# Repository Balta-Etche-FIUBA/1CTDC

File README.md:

"# 1CTDC" 
Esto es algo que sumo Git ni idea

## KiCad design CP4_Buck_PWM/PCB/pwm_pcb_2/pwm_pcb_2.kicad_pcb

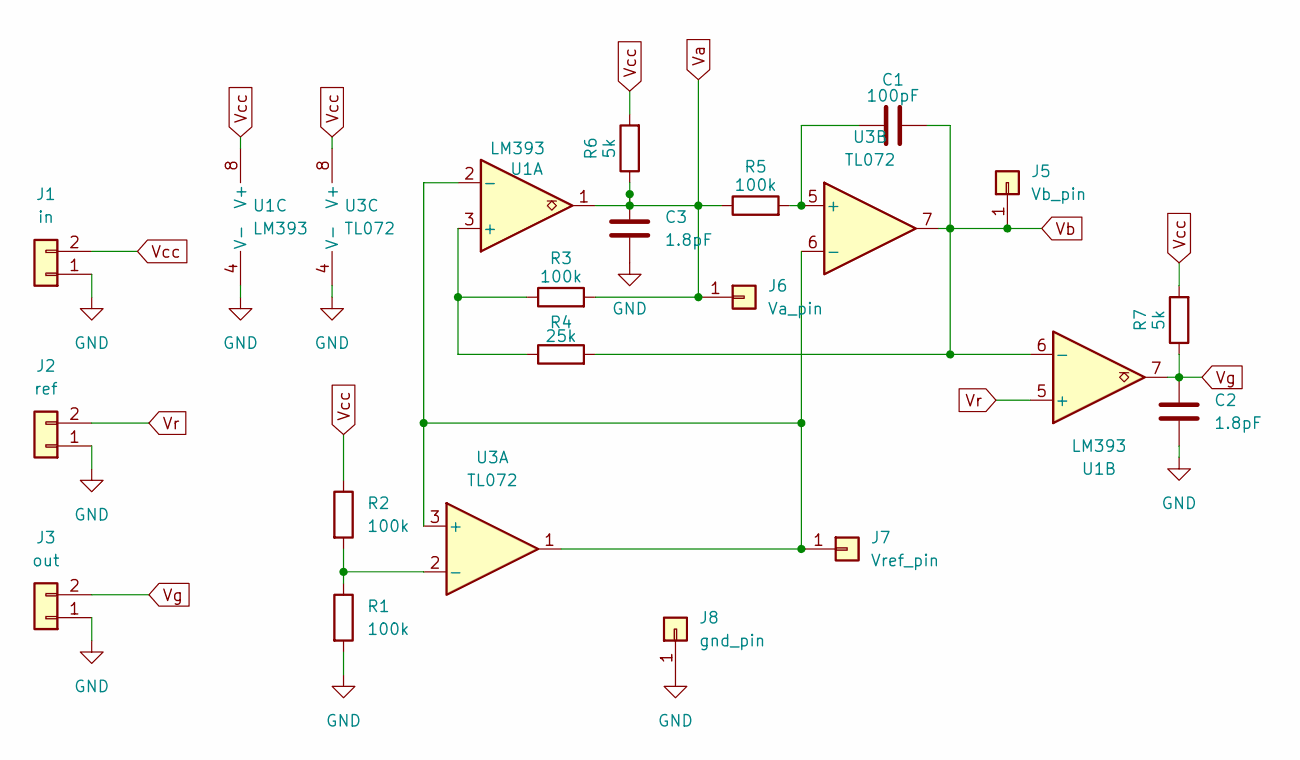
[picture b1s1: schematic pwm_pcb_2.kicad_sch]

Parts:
C1: 100pF; C_Disc_D4.3mm_W1.9mm_P5.00mm
C2, C3: 1.8pF; C_Disc_D4.3mm_W1.9mm_P5.00mm
J1: in; TerminalBlock_Phoenix_MKDS-1,5-2-5.08_1x02_P5.08mm_Horizont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
J2: ref; TerminalBlock_Phoenix_MKDS-1,5-2-5.08_1x02_P5.08mm_Horizont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
J3: out; TerminalBlock_Phoenix_MKDS-1,5-2-5.08_1x02_P5.08mm_Horizont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
J5: Vb_pin; PinHeader_1x01_P2.54mm_Vertical
J6: Va_pin; PinHeader_1x01_P2.54mm_Vertical
J7: Vref_pin; PinHeader_1x01_P2.54mm_Vertical
J8: gnd_pin; PinHeader_1x01_P2.54mm_Vertical
R1, R2, R3: 100k; R_Axial_DIN0204_L3.6mm_D1.6mm_P7.62mm_Horizontal
R4: 25k; R_Axial_DIN0204_L3.6mm_D1.6mm_P7.62mm_Horizontal
R5: 100k; Potentiometer_Bourns_3296W_Vertical
R6, R7: 5k; R_Axial_DIN0204_L3.6mm_D1.6mm_P7.62mm_Horizontal
U1: LM393; DIP-8_W7.62mm
U3: TL072; DIP-8_W7.62mm

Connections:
GND: C2.2, C3.2, J1.1, J2.1, J3.1, J8.1, R1.2, U1.4 (V-), U3.4 (V-)
unnamed: J7.1, U1.2 (-), U3.1, U3.3 (+), U3.6 (-)
unnamed: R3.1, R4.1, U1.3 (+)
unnamed: R1.1, R2.2, U3.2 (-)
unnamed: C1.1, R5.2, U3.5 (+)
Va: C3.1, J6.1, R3.2, R5.1, R6.1, U1.1
Vb: C1.2, J5.1, R4.2, U1.6 (-), U3.7
Vcc: J1.2, R2.1, R6.2, R7.2, U1.8 (V+), U3.8 (V+)
Vg: C2.1, J3.2, R7.1, U1.7
Vr: J2.2, U1.5 (+)

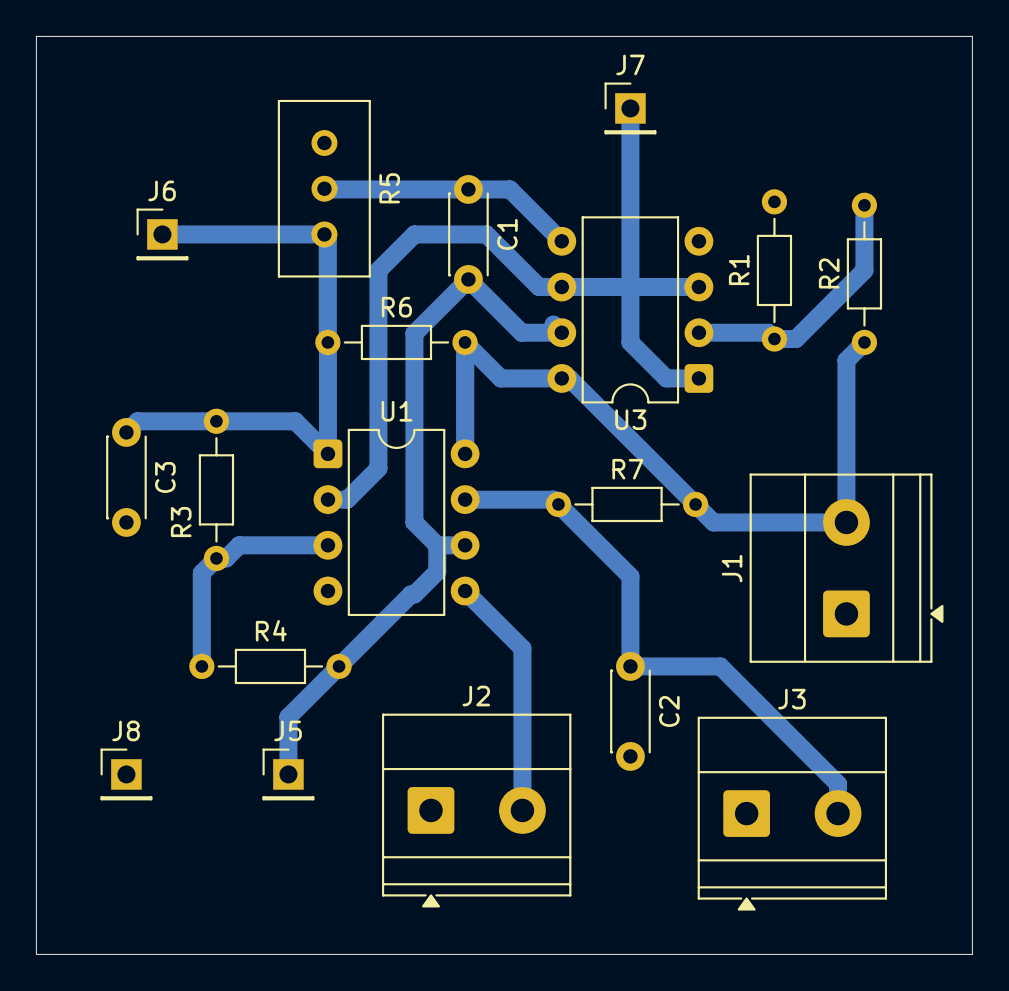
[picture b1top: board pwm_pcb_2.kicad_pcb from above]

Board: 2 copper layers, 52.0 x 51.0 mm, 19 parts (0 on the bottom side), 10 nets.

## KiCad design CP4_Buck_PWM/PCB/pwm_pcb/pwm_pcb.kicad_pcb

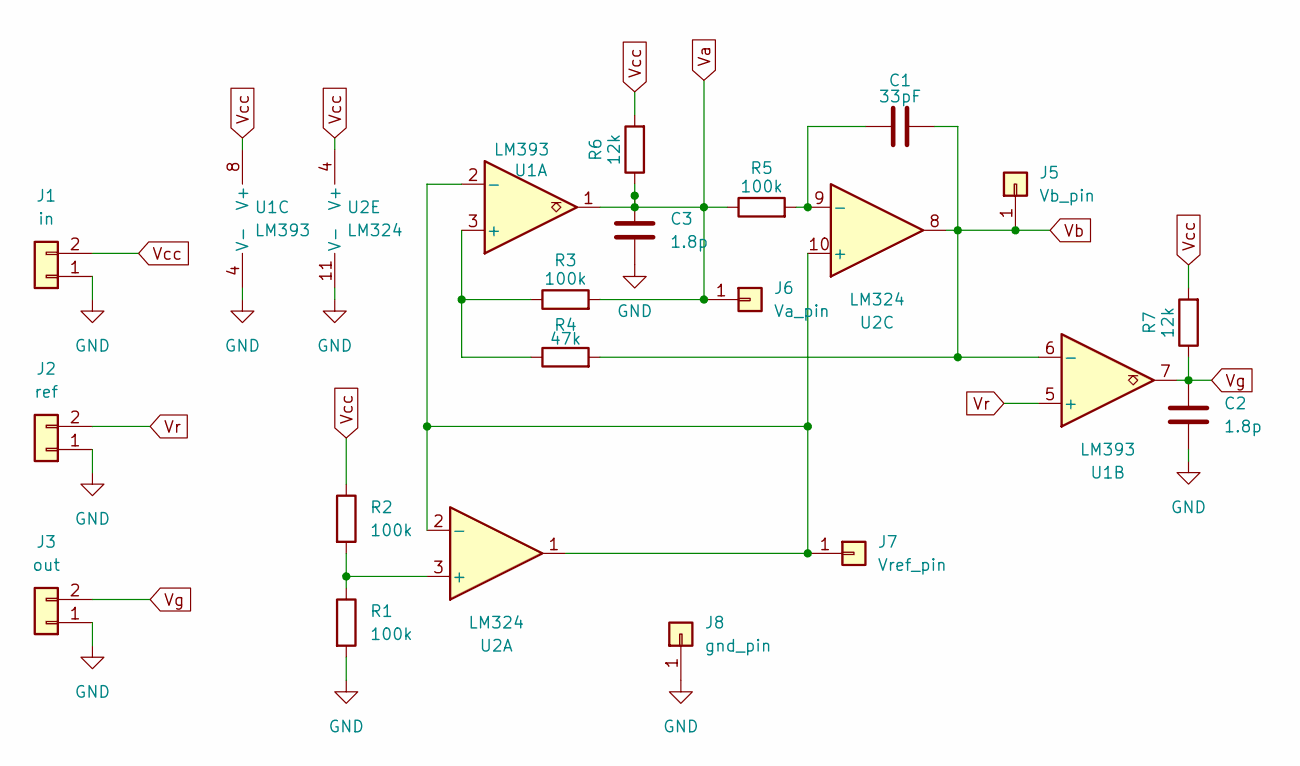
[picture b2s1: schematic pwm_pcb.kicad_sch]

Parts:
C1: 33pF; C_Disc_D3.0mm_W1.6mm_P2.50mm
C2, C3: 1.8p; C_Disc_D3.0mm_W1.6mm_P2.50mm
J1: in; TerminalBlock_Phoenix_MKDS-1,5-2-5.08_1x02_P5.08mm_Horizont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
J2: ref; TerminalBlock_Phoenix_MKDS-1,5-2-5.08_1x02_P5.08mm_Horizont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
J3: out; TerminalBlock_Phoenix_MKDS-1,5-2-5.08_1x02_P5.08mm_Horizont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
J5: Vb_pin; PinHeader_1x01_P2.54mm_Vertical
J6: Va_pin; PinHeader_1x01_P2.54mm_Vertical
J7: Vref_pin; PinHeader_1x01_P2.54mm_Vertical
J8: gnd_pin; PinHeader_1x01_P2.54mm_Vertical
R1, R2, R3: 100k; R_Axial_DIN0204_L3.6mm_D1.6mm_P5.08mm_Horizontal
R4: 47k; R_Axial_DIN0204_L3.6mm_D1.6mm_P5.08mm_Horizontal
R5: 100k; Potentiometer_Bourns_3296W_Vertical
R6, R7: 12k; R_Axial_DIN0204_L3.6mm_D1.6mm_P5.08mm_Horizontal
U1: LM393; DIP-8_W7.62mm
U2: LM324; DIP-14_W7.62mm

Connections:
GND: C2.2, C3.2, J1.1, J2.1, J3.1, J8.1, R1.2, U1.4 (V-), U2.11 (V-)
unnamed: J7.1, U1.2 (-), U2.1, U2.2 (-), U2.10 (+)
unnamed: R3.1, R4.1, U1.3 (+)
unnamed: R1.1, R2.2, U2.3 (+)
unnamed: C1.1, R5.2, U2.9 (-)
Va: C3.1, J6.1, R3.2, R5.1, R6.1, U1.1
Vb: C1.2, J5.1, R4.2, U1.6 (-), U2.8
Vcc: J1.2, R2.1, R6.2, R7.2, U1.8 (V+), U2.4 (V+)
Vg: C2.1, J3.2, R7.1, U1.7
Vr: J2.2, U1.5 (+)

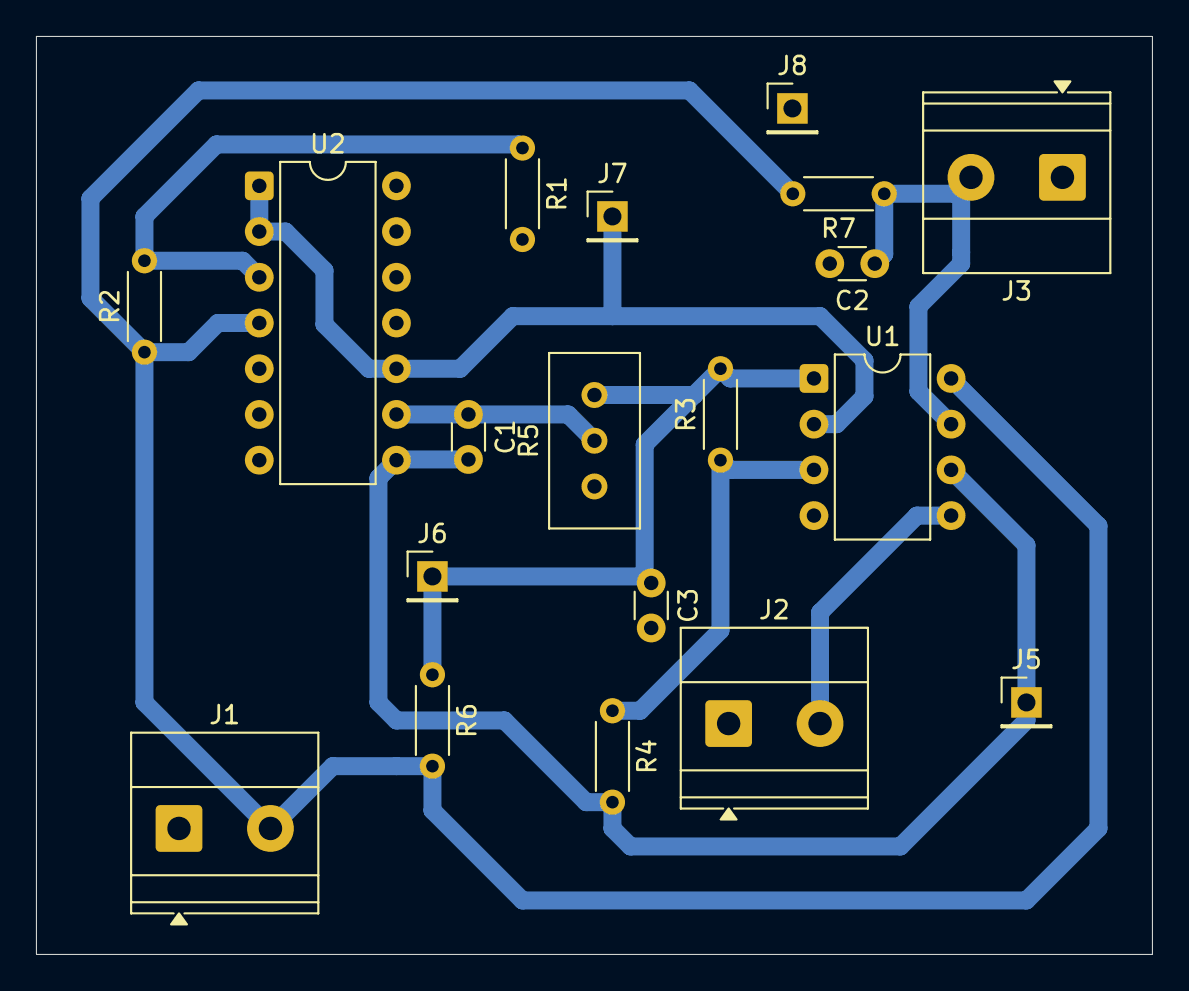
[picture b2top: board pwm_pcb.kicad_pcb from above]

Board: 2 copper layers, 62.0 x 51.0 mm, 19 parts (0 on the bottom side), 10 nets.

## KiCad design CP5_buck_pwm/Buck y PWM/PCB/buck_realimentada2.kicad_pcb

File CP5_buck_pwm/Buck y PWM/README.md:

Solo porque sino no me dejaba crear la carpeta

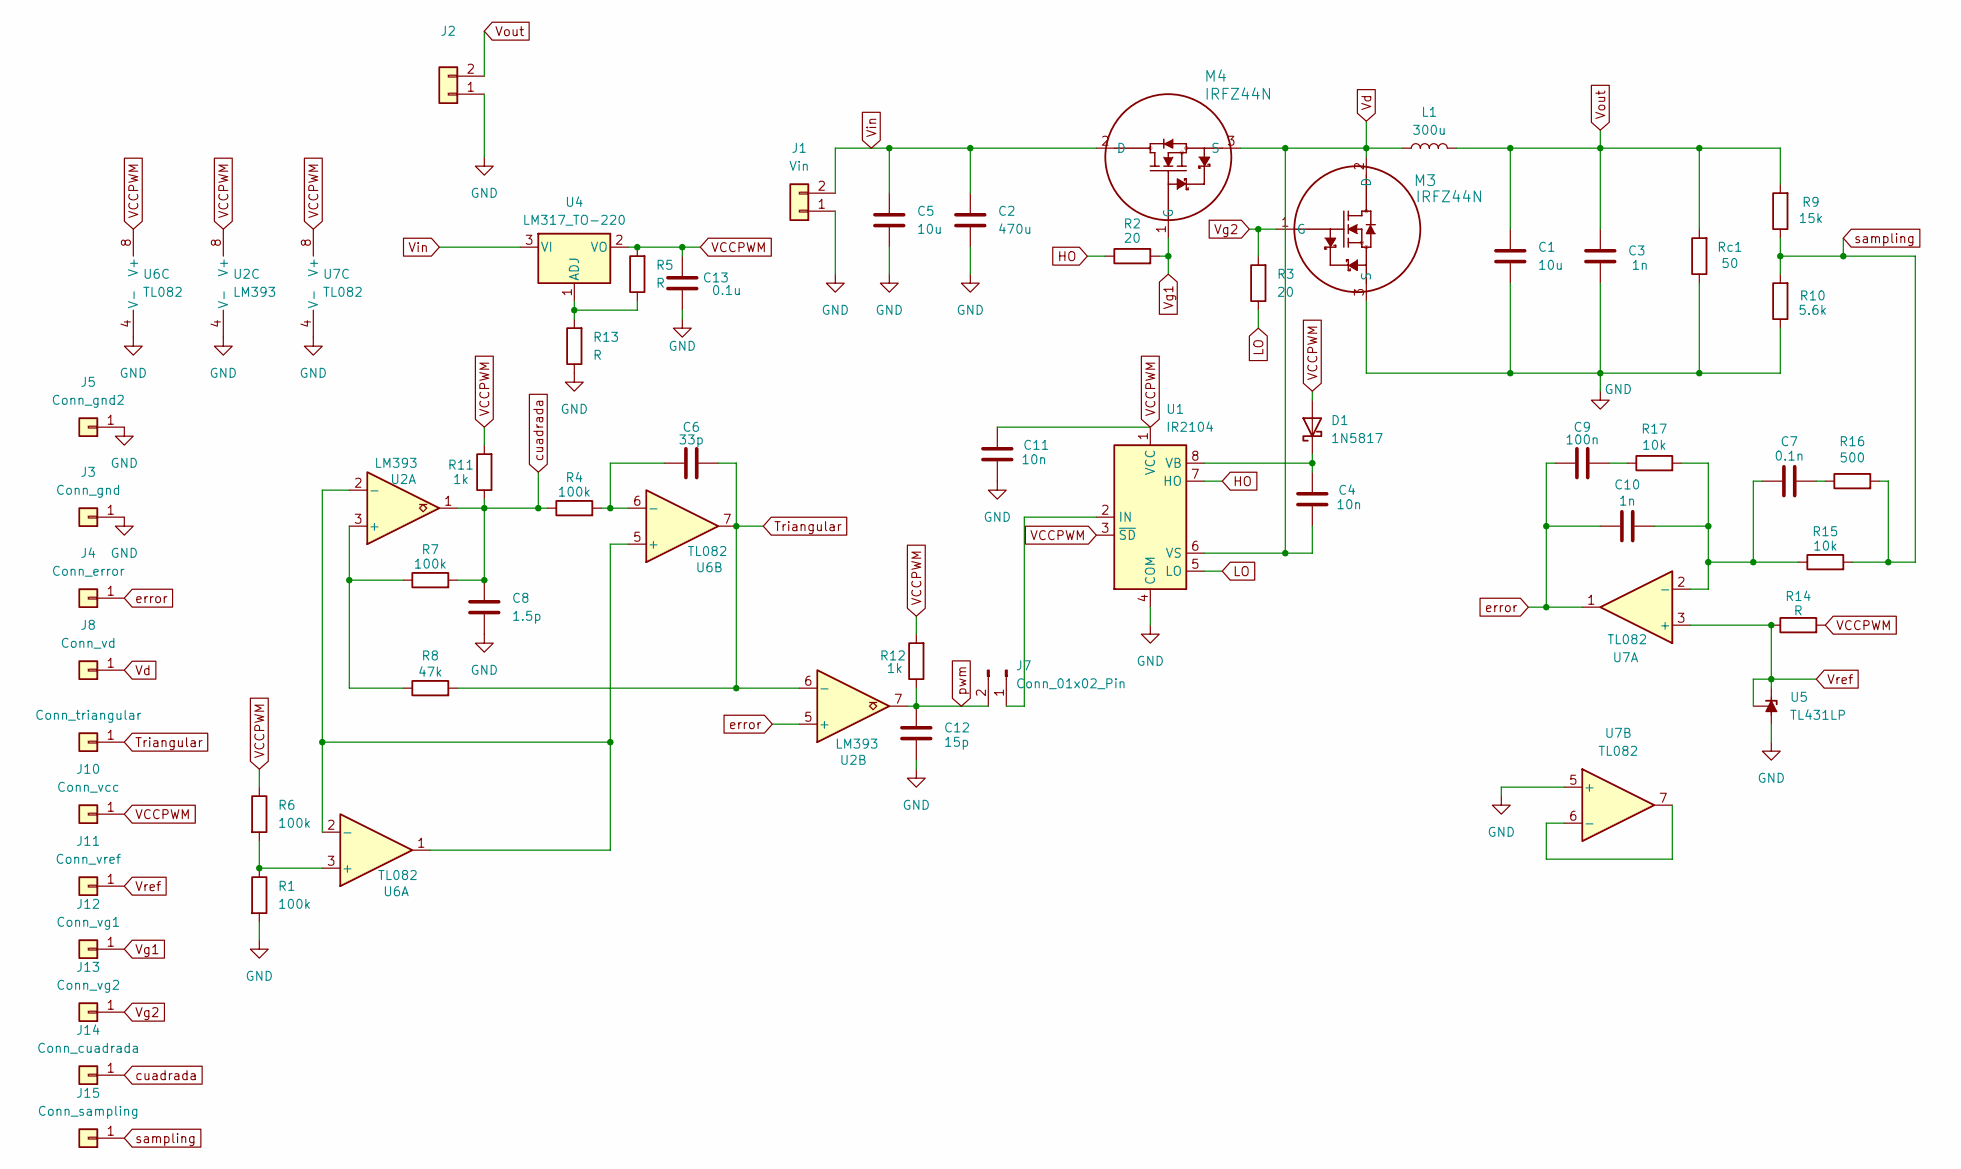
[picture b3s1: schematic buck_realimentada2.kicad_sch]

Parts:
C1: 10u; C_Disc_D4.3mm_W1.9mm_P5.00mm
C2: 470u; CP_Radial_D10.0mm_P5.00mm
C3, C10: 1n; C_Disc_D4.3mm_W1.9mm_P5.00mm
C4, C11: 10n; C_Disc_D4.3mm_W1.9mm_P5.00mm
C5: 10u; CP_Radial_D4.0mm_P2.00mm
C6: 33p; C_Disc_D4.3mm_W1.9mm_P5.00mm
C7: 0.1n; C_Disc_D4.3mm_W1.9mm_P5.00mm
C8: 1.5p; C_Disc_D4.3mm_W1.9mm_P5.00mm
C9: 100n; C_Disc_D4.3mm_W1.9mm_P5.00mm
C12: 15p; C_Disc_D4.3mm_W1.9mm_P5.00mm
C13: 0.1u; C_Disc_D4.3mm_W1.9mm_P5.00mm
D1: 1N5817; D_DO-41_SOD81_P10.16mm_Horizontal
J1: Vin; TerminalBlock_Phoenix_MKDS-1,5-2-5.08_1x02_P5.08mm_Horizont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
J2: Vout; TerminalBlock_Phoenix_MKDS-1,5-2-5.08_1x02_P5.08mm_Horizont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
J3: Conn_gnd; PinHeader_1x01_P2.54mm_Vertical
J4: Conn_error; PinHeader_1x01_P2.54mm_Vertical
J5: Conn_gnd2; PinHeader_1x01_P2.54mm_Vertical
J6: Conn_triangular; PinHeader_1x01_P2.54mm_Vertical
J7: Conn_01x02_Pin; PinHeader_1x02_P2.54mm_Vertical
J8: Conn_vd; PinHeader_1x01_P2.54mm_Vertical
J10: Conn_vcc; PinHeader_1x01_P2.54mm_Vertical
J11: Conn_vref; PinHeader_1x01_P2.54mm_Vertical
J12: Conn_vg1; PinHeader_1x01_P2.54mm_Vertical
J13: Conn_vg2; PinHeader_1x01_P2.54mm_Vertical
J14: Conn_cuadrada; PinHeader_1x01_P2.54mm_Vertical
J15: Conn_sampling; PinHeader_1x01_P2.54mm_Vertical
L1: 300u; Untitled
M3, M4: IRFZ44N; TO-220-3_Vertical
R1, R6, R7: 100k; R_Axial_DIN0204_L3.6mm_D1.6mm_P7.62mm_Horizontal
R2, R3: 20; R_Axial_DIN0204_L3.6mm_D1.6mm_P7.62mm_Horizontal
R4: 100k; Potentiometer_Bourns_3296W_Vertical
R5, R14: R; R_Axial_DIN0204_L3.6mm_D1.6mm_P7.62mm_Horizontal
R8: 47k; R_Axial_DIN0204_L3.6mm_D1.6mm_P7.62mm_Horizontal
R9: 15k; R_Axial_DIN0204_L3.6mm_D1.6mm_P7.62mm_Horizontal
R10: 5.6k; R_Axial_DIN0204_L3.6mm_D1.6mm_P7.62mm_Horizontal
R11, R12: 1k; R_Axial_DIN0204_L3.6mm_D1.6mm_P7.62mm_Horizontal
R13: R; Potentiometer_Bourns_3296W_Vertical
R15, R17: 10k; R_Axial_DIN0204_L3.6mm_D1.6mm_P7.62mm_Horizontal
R16: 500; R_Axial_DIN0204_L3.6mm_D1.6mm_P7.62mm_Horizontal
Rc1: 50; Potentiometer_Bourns_3296W_Vertical
U1: IR2104; DIP-8_W7.62mm
U2: LM393; DIP-8_W7.62mm
U4: LM317_TO-220; TO-220-3_Vertical
U5: TL431LP; TO-92_Inline_Wide
U6, U7: TL082; DIP-8_W7.62mm

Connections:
GND: C1.2, C2.2, C3.2, C5.2, C8.2, C11.2, C12.2, C13.2, J1.1, J2.1, J3.1, J5.1, M3.3 (S), R1.2, R10.1, R13.1, Rc1.1, U1.4 (COM), U2.4 (V-), U5.2 (A), U6.4 (V-), U7.4 (V-), U7.5 (+)
HO: R2.1, U1.7 (HO)
LO: R3.1, U1.5 (LO)
unnamed: C7.2, R16.1
unnamed: C9.2, R17.1
unnamed: C4.1, D1.1 (K), U1.8 (VB)
unnamed: J7.1, U1.2 (IN)
unnamed: R7.1, R8.1, U2.3 (+)
unnamed: U2.2 (-), U6.1, U6.2 (-), U6.5 (+)
unnamed: R5.1, R13.2, U4.1 (ADJ)
unnamed: R1.1, R6.2, U6.3 (+)
unnamed: C6.1, R4.2, U6.6 (-)
unnamed: C7.1, C10.2, R15.1, R17.2, U7.2 (-)
unnamed: U7.6 (-), U7.7
Triangular: C6.2, J6.1, R8.2, U2.6 (-), U6.7
VCCPWM: C11.1, C13.1, D1.2 (A), J10.1, R5.2, R6.1, R11.2, R12.2, R14.2, U1.1 (VCC), U1.3 (~SD), U2.8 (V+), U4.2 (VO), U6.8 (V+), U7.8 (V+)
Vd: C4.2, J8.1, L1.1, M3.2 (D), M4.3 (S), U1.6 (VS)
Vg1: J12.1, M4.1 (G), R2.2
Vg2: J13.1, M3.1 (G), R3.2
Vin: C2.1, C5.1, J1.2, M4.2 (D), U4.3 (VI)
Vout: C1.1, C3.1, J2.2, L1.2, R9.2, Rc1.2
Vref: J11.1, R14.1, U5.1 (REF), U5.3 (K), U7.3 (+)
cuadrada: C8.1, J14.1, R4.1, R7.2, R11.1, U2.1
error: C9.1, C10.1, J4.1, U2.5 (+), U7.1
pwm: C12.1, J7.2, R12.1, U2.7
sampling: J15.1, R9.1, R10.2, R15.2, R16.2

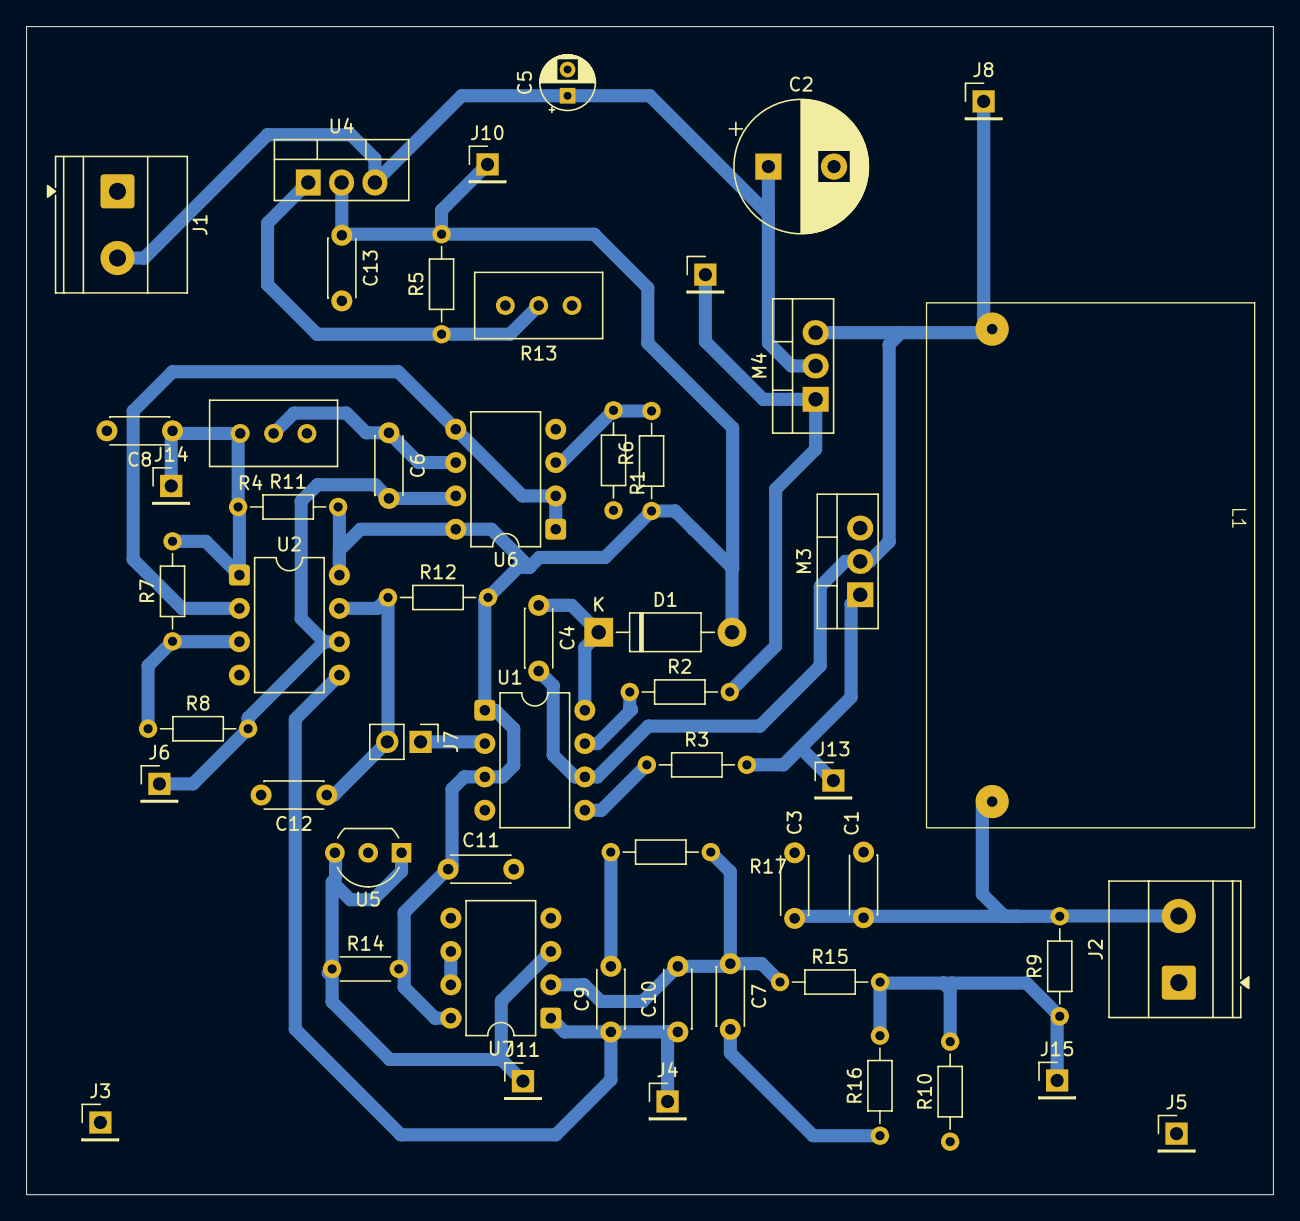
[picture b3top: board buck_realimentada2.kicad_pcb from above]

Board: 2 copper layers, 95.0 x 89.0 mm, 54 parts (0 on the bottom side), 26 nets.

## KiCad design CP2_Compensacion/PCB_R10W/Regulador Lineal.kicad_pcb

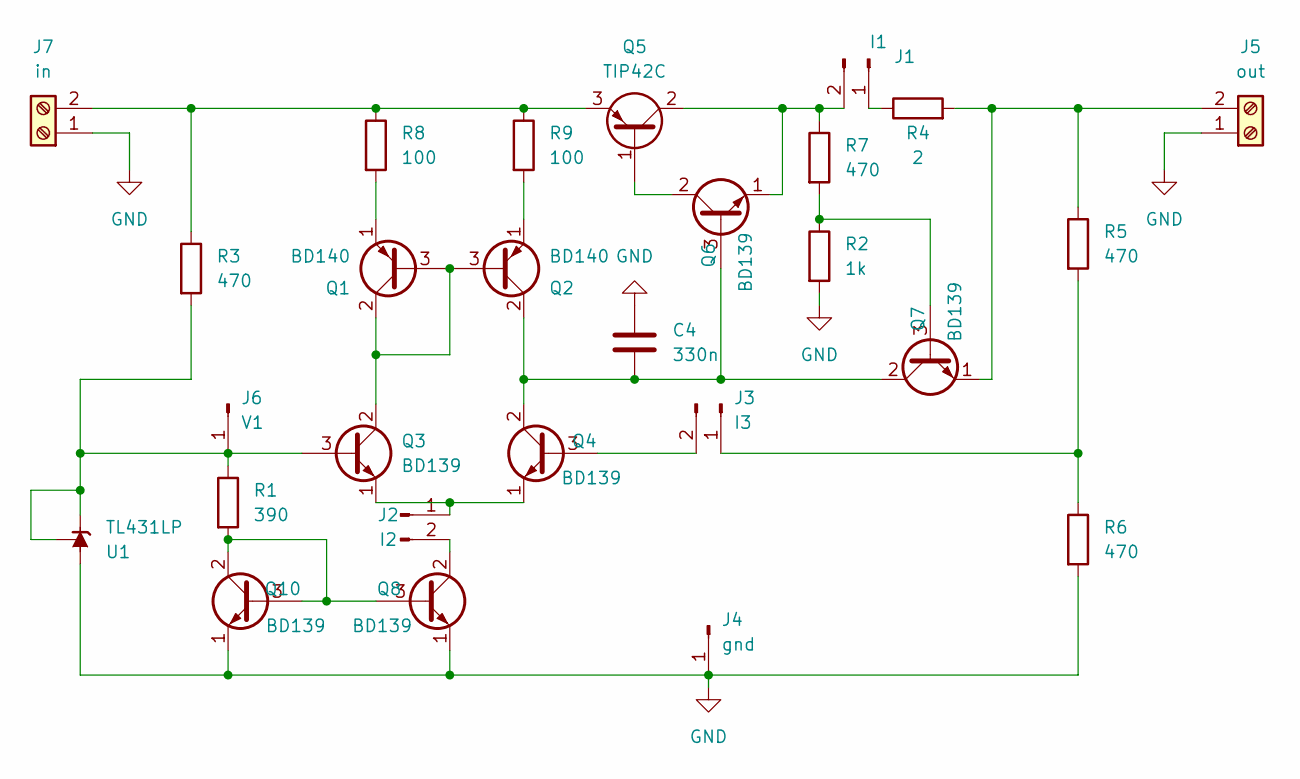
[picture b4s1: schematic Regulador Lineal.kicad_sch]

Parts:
C4: 330n; C_Disc_D4.3mm_W1.9mm_P5.00mm
J1: I1; PinHeader_1x02_P2.54mm_Vertical
J2: I2; PinHeader_1x02_P2.54mm_Vertical
J3: I3; PinHeader_1x02_P2.54mm_Vertical
J4: gnd; PinHeader_1x01_P2.54mm_Vertical
J5: out; TerminalBlock_Phoenix_MKDS-1,5-2-5.08_1x02_P5.08mm_Horizont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
J6: V1; PinHeader_1x01_P2.54mm_Vertical
J7: in; TerminalBlock_Phoenix_MKDS-1,5-2-5.08_1x02_P5.08mm_Horizont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
Q1, Q2: BD140; TO-126-3_Vertical
Q3, Q4, Q6, Q7, Q8, Q10: BD139; TO-126-3_Vertical
Q5: TIP42C; TO-220-3_Vertical
R1: 390; R_Axial_DIN0204_L3.6mm_D1.6mm_P5.08mm_Horizontal
R2: 1k; R_Axial_DIN0204_L3.6mm_D1.6mm_P5.08mm_Horizontal
R3, R5, R6, R7: 470; R_Axial_DIN0204_L3.6mm_D1.6mm_P5.08mm_Horizontal
R4: 2; R_Axial_DIN0204_L3.6mm_D1.6mm_P5.08mm_Horizontal
R8, R9: 100; R_Axial_DIN0204_L3.6mm_D1.6mm_P5.08mm_Horizontal
U1: TL431LP; TO-92_Inline

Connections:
GND: C4.1, J4.1, J5.1, J7.1, Q8.1 (E), Q10.1 (E), R2.2, R6.2, U1.2 (A)
unnamed: J1.1, R4.1
unnamed: J1.2, Q5.2 (C), Q6.1 (E), R7.1
unnamed: J2.1, Q3.1 (E), Q4.1 (E)
unnamed: J2.2, Q8.2 (C)
unnamed: J3.1, R5.2, R6.1
unnamed: J3.2, Q4.3 (B)
unnamed: J5.2, Q7.1 (E), R4.2, R5.1
unnamed: J6.1, Q3.3 (B), R1.1, R3.2, U1.1 (REF), U1.3 (K)
unnamed: J7.2, Q5.3 (E), R3.1, R8.1, R9.1
unnamed: Q1.2 (C), Q1.3 (B), Q2.3 (B), Q3.2 (C)
unnamed: Q1.1 (E), R8.2
unnamed: C4.2, Q2.2 (C), Q4.2 (C), Q6.3 (B), Q7.2 (C)
unnamed: Q2.1 (E), R9.2
unnamed: Q5.1 (B), Q6.2 (C)
unnamed: Q7.3 (B), R2.1, R7.2
unnamed: Q8.3 (B), Q10.2 (C), Q10.3 (B), R1.2

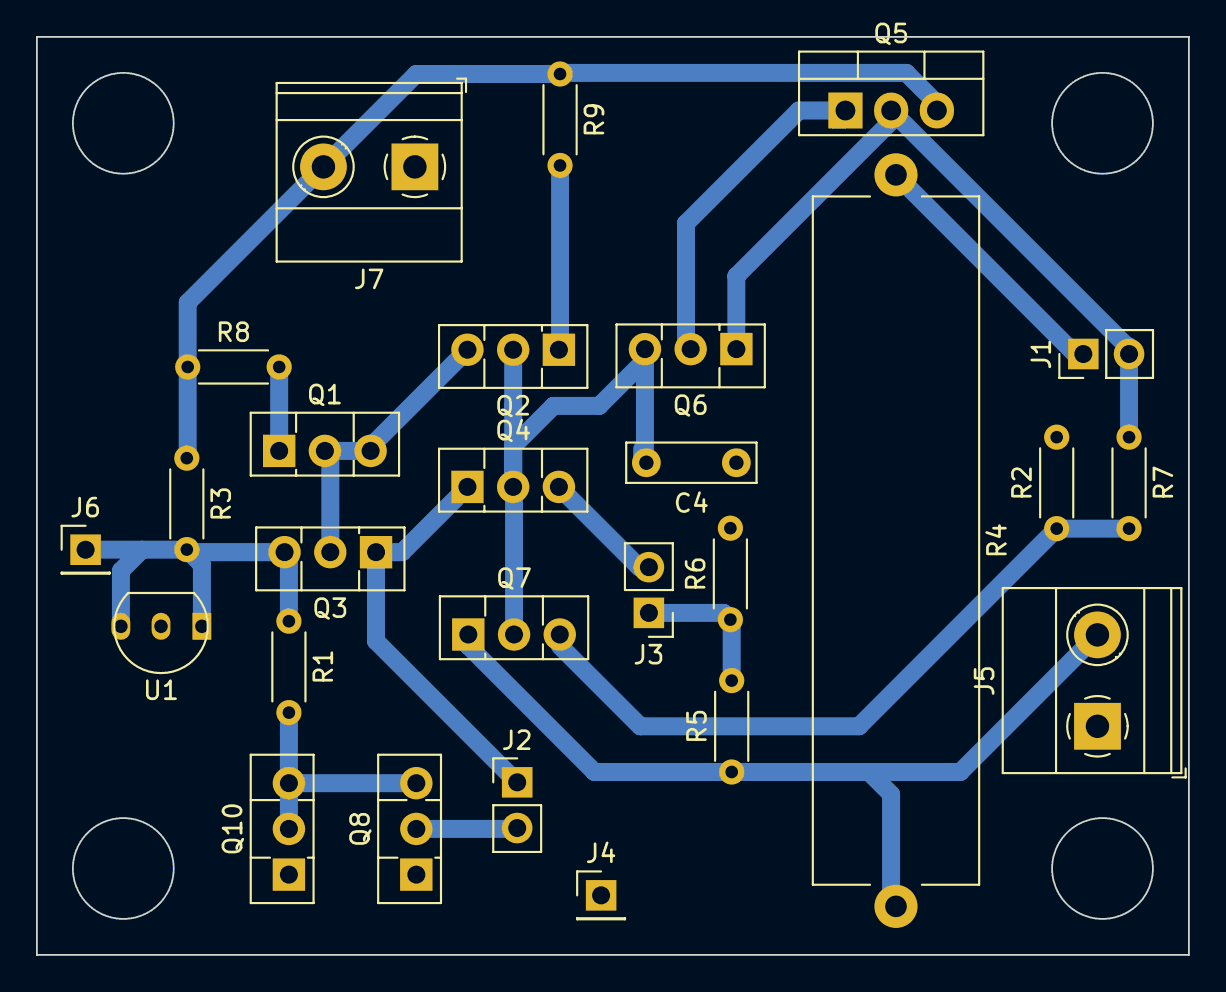
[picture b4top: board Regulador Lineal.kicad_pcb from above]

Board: 2 copper layers, 64.0 x 51.0 mm, 27 parts (0 on the bottom side), 17 nets.

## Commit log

2025-03-26 Material
2025-03-31 Add files via upload
    Sumo regulador de tension y fuente de corriente
2025-03-31 Create README.md
    Datasheet
2025-03-31 Create Modelos_LTspice
2025-03-31 Create LTspice
2025-04-01 Add files via upload
    Cambios en resistencia de Foldback -> Icc = 0.427, Imax = 1.507 (creo, no me acuerdo bien)
2025-04-01 Graficos y codigo para jugar con los graficos
    Le falta todavia una vuelta de rosca para que sean mas lindos
2025-04-04 Add files via upload
    Simulación AC para la ganancia de lazo
2025-04-05 Creado con Colab
2025-04-05 Revert "Creado con Colab"
    This reverts commit ba9da68d6c6265d1acb79198899e3a9c7971e195.
2025-04-11 Add files via upload
    Corrección de la regulación de la tensión de salida de 5V.
2025-04-16 Create a
2025-04-16 Add files via upload
    Esquematico para simulacion AC
2025-04-19 Add files via upload
    Hola de datos del transistor de paso
2025-04-22 Add files via upload
    Looool
2025-04-22 Add files via upload
    loool
2025-04-22 Create a
    Modelos para usar el KiCAD
2025-04-24 Correcion del esquematico KiCad
2025-04-24 Correcion esquematico KiCad II
2025-04-25 Add files via upload
    Corrección corte de tierra
2025-04-28 pista mal enrutada
2025-04-29 PCB ok
2025-04-30 AgreGo resistencia de 10w
2025-04-30 Archivos de Fabricacion
2025-05-04 Backups
2025-05-04 Carpetas ok
2025-05-04 test
2025-05-08 Create a.txt
    a
2025-05-08 Add files via upload
    Mediciones de Vout para distintas RL
2025-05-09 Create CP3_Mediciones
2025-05-09 Add files via upload
    Agregué el modelo del TL431, y actualicé valores de resistencias
2025-05-09 Rename Regulacion de linea .xlsx to MedicionesRegulacion de linea .xlsx
2025-05-09 Rename mediciones.xlsx to mediciones.xlsx
2025-05-09 Rename MedicionesRegulacion de linea .xlsx to Regulacion de linea .xlsx
2025-05-10 TP2 actualizado
2025-05-17 Regula medianamente bien
    Regula siempre entre 9V y 10V, hay que cambiar la Vin y el Ton según el excel. Después hay que ajustar bien los valores de RL y C para mejorar la respuesta
2025-05-22 Create Cálculo especificaciones L
2025-05-22 Modelo spice del TL081
2025-05-23 Datasheets componentes buck
2025-05-24 buck nmos OK
2025-05-25 Buck funcionando tension y corriente ok
2025-05-25 Buck tension y corriente ok
2025-05-25 IRFZ44N
2025-05-25 Clase Tecnología de componentes
2025-05-26 Resistencia, capacitor y conexion de gate driver
2025-05-27 Archivos de salida el PCB
2025-05-28 scrip para hallar R5
2025-05-30 Simulacion frecuancia baja
2025-05-31 Buck_ok
2025-06-02 Buck_nmos_final
2025-06-02 bucknomos
2025-06-02 new_file
2025-06-02 driver + bick pero aesthetic
2025-06-02 file
2025-06-03 driver_ok
2025-06-04 Fuente buck + PWM andando
    Tratenlo con amor q si lo miras mal se rompe
2025-06-04 Buck + PWM andando
    + todo lo q necesitan para correr
2025-06-04 Delete CP5_buck_pwm/buck_pwm.asc
    lo metí en la carpeta Buck + PWM
2025-06-11 lazo cerrado
2025-06-14 intento 3 con otra compensacion
2025-06-16 Realimentacion con R comerciales
2025-06-16 realimentacion
2025-06-17 No estabiliza con fuente de 10V
2025-06-17 add intento6_error estabilizacion de lazo ok
2025-06-18 Add catalogo abebashop
2025-06-18 PCB, falta solucionar un problema de tierra aislada
2025-06-18 add lm317L
2025-06-18 PCB terminado
2025-06-19 PCB revisado
2025-06-19 agregué corte de tierra
2025-06-19 Archivos de salida
2025-06-23 PCB corregida
2025-06-23 coor
2025-06-23 compensacion 2
2025-06-23 Acomodar pistas gnd y nuevo capacitor
2025-06-25 PCB en proceso
2025-06-27 Disipador y Caclulo de potencia
2025-06-28 compensacion
2025-06-30 Last RR
2025-07-06 Compensacion OK
2025-07-19 Carpetas ordenadas
2025-07-19 Carpetas ordenadas final
